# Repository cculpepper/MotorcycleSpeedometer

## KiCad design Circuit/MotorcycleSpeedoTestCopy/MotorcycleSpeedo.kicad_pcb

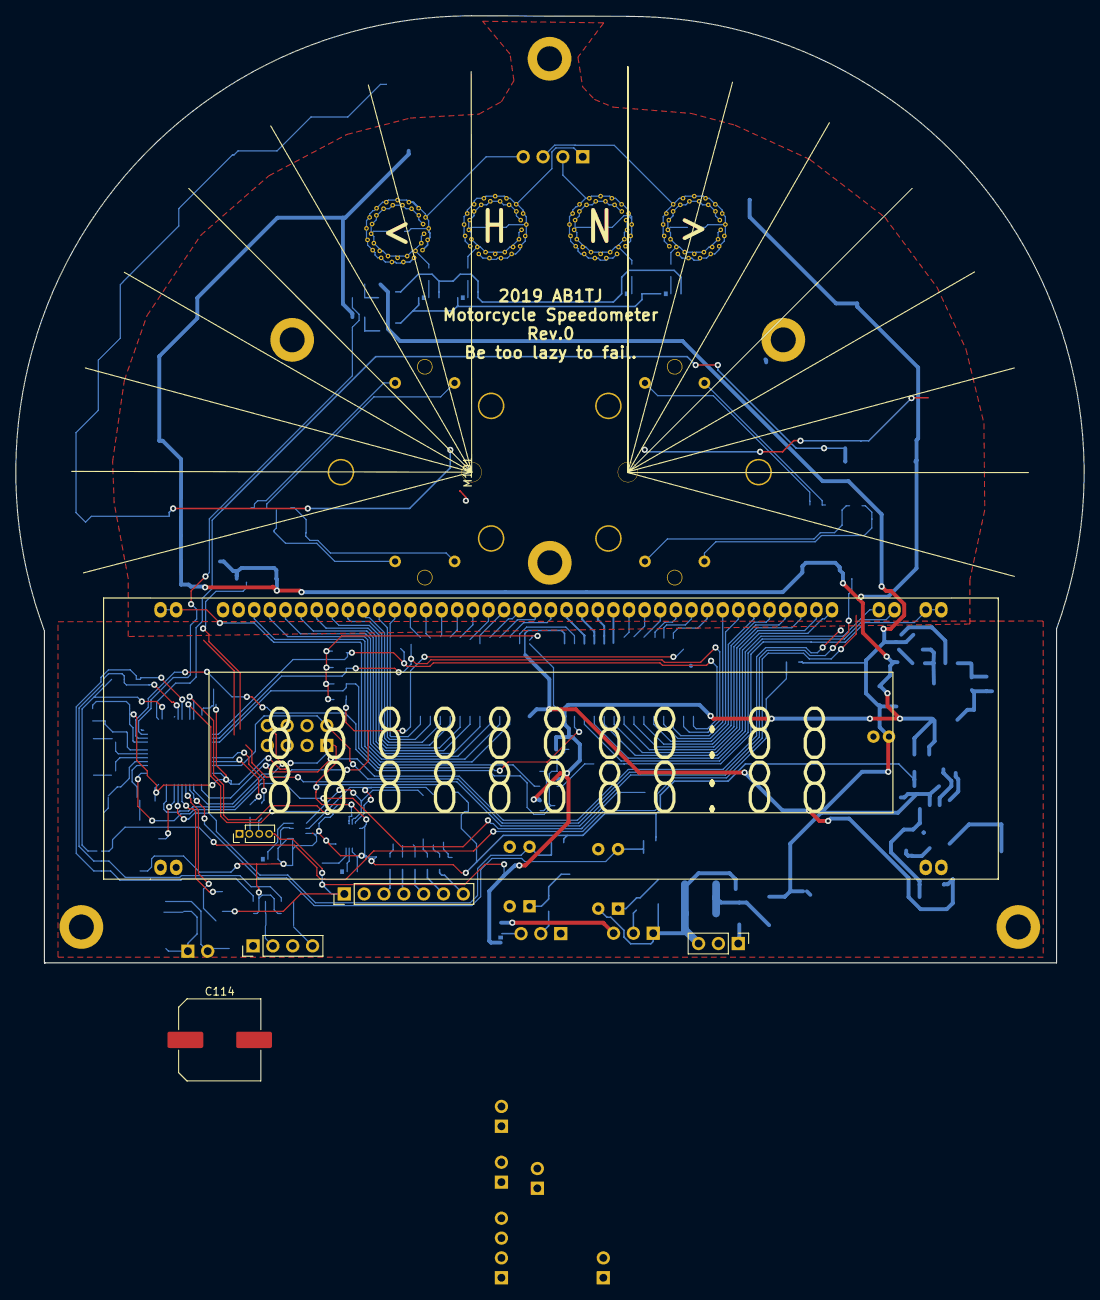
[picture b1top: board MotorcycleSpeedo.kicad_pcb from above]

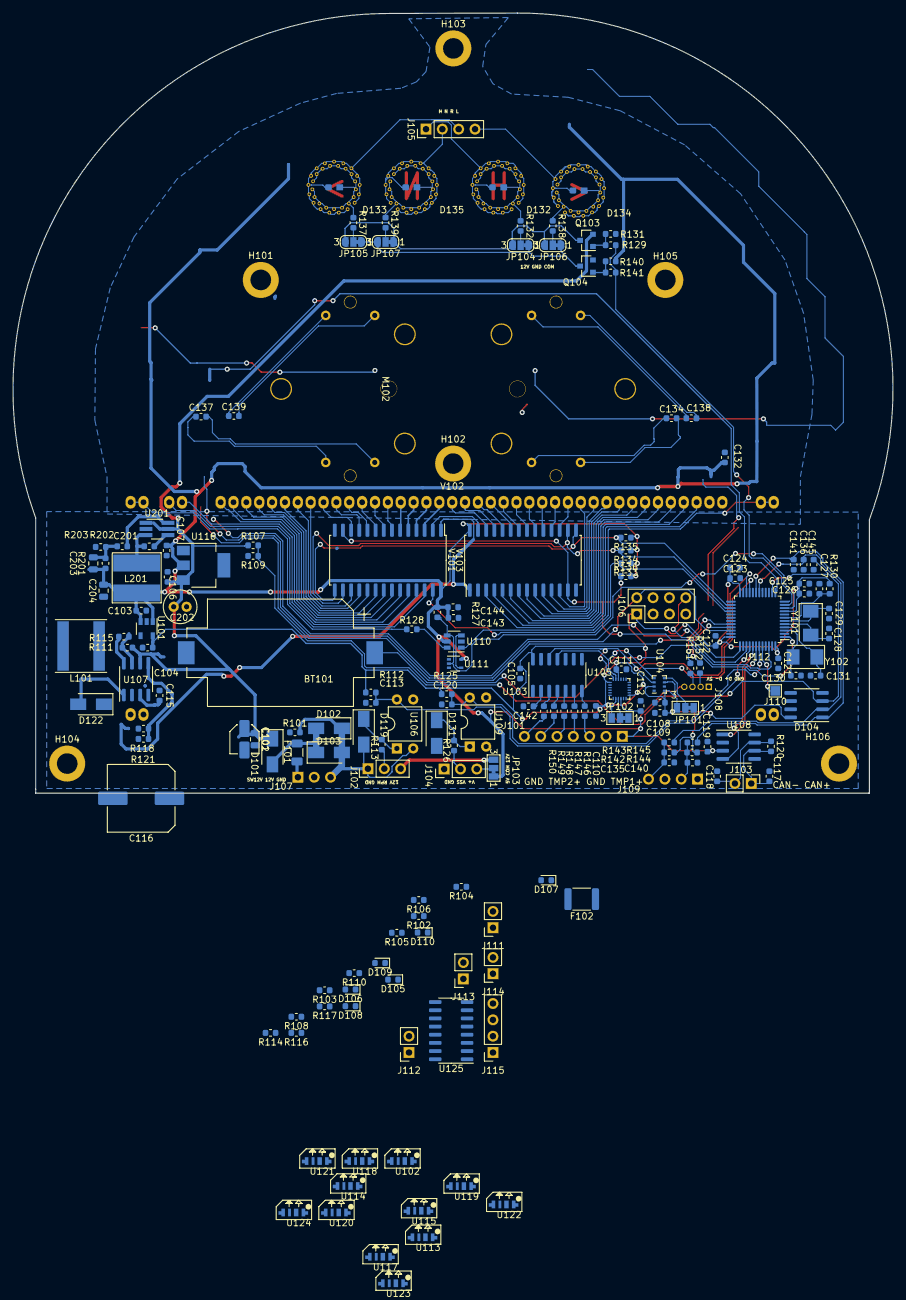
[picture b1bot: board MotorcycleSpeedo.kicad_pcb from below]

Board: 2 copper layers, 136.8 x 121.3 mm, 184 parts (167 on the bottom side), 159 nets.

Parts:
BT101: Battery_Cell; BatteryHolder_Keystone_1060_1x2032
C101: C; C_0805_2012Metric
C102: 33uH; C_Elec_4x5.4
C103, C104, C106, C107, C108, C110, C113, C117, C118, C119, C120, C121, C122, C132, C145: C; C_0603_1608Metric
C105, C134, C137, C138, C139, C143, C144: .1uF; C_0603_1608Metric
C109, C111, C112: .1uf; C_0603_1608Metric
C114: CP1; C_Elec_10x10.2
C115: 680pf; C_0603_1608Metric
C116: 330uF; C_Elec_10x10.2
C123, C126, C127, C135, C140: 0.1uF; C_0603_1608Metric
C124, C125, C201: 1uF; C_0603_1608Metric
C128, C129: 20pF; C_0603_1608Metric
C130, C131: 9pF; C_0603_1608Metric
C136, C141: 0.22uF; C_0603_1608Metric
C142: .01uF; C_0603_1608Metric
C202: 22uF; C_Radial_D5.0mm_H11.0mm_P2.00mm
C203: DNP; C_0805_2012Metric
C204: 22uF; C_0805_2012Metric
D101, D102: D_Schottky; D_SMA
D103: D_TVS; D_SMA
D104: SP721; SOIC-8_3.9x4.9mm_P1.27mm
D105, D106, D107, D108, D109, D110: LED; LED_0603_1608Metric
D119, D122, D131: D; D_SMA
D132: HIGH; HF.SilkSF.Cu
D133: RIGHT; RightPointingF.SilkSF.Cu
D134: LEFT; LeftPointingF.SilkSF.Cu
D135: NEUTRAL; NF.SilkSF.Cu
F101: Polyfuse; Fuse_1206_3216Metric
F102: Polyfuse; Fuse_1812_4532Metric
H101, H102, H103, H104, H105, H106: MountingHole_Pad; MountingHole_3.2mm_M3_DIN965_Pad
J101: Conn_01x07_Female; PinHeader_1x07_P2.54mm_Vertical
J102, J104, J107: Conn_01x03_Female; PinHeader_1x03_P2.54mm_Vertical
J103: Conn_01x02_Female; PinHeader_1x02_P2.54mm_Vertical
J105, J109: Conn_01x04_Female; PinHeader_1x04_P2.54mm_Vertical
J106: Conn_02x04_Counter_Clockwise; PinHeader_2x04_P2.54mm_Vertical
J108: Conn_01x04_Male; PinHeader_1x04_P1.27mm_Vertical
J110: Conn_01x01_Female; TestPoint_Pad_1.5x1.5mm
J111, J112, J113, J114: Conn_01x02_Male; PinSocket_1x02_P2.54mm_Vertical
J115: Conn_01x04_Female; PinSocket_1x04_P2.54mm_Vertical
JP101, JP102, JP103: SolderJumper_3_Bridged12; SolderJumper-3_P1.3mm_Bridged12_Pad1.0x1.5mm_NumberLabels
JP104, JP105, JP106, JP107: SolderJumper_3_Bridged12; SolderJumper-3_P1.3mm_Bridged12_RoundedPad1.0x1.5mm_NumberL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
L101: 330uh; L_Taiyo-Yuden_NR-80xx
L201: 10uH; CDRH6D28
M101, M102: Stepper_Motor_bipolar; x25FrontStepper
Q103: Q_PMOS_GSD; SOT-23
Q104: Q_NMOS_GSD; SOT-23
R101, R110, R113, R117, R126, R127, R128, R130, R132, R137, R138, R139: R; R_0603_1608Metric
R102, R103, R104, R105, R106, R108: 1K; R_0603_1608Metric
R107, R112, R114, R116, R125, R131, R133, R134, R135, R136, R140: 10K; R_0603_1608Metric
R109, R143, R145: 470; R_0603_1608Metric
R111: .22; R_0603_1608Metric
R115: 180; R_0603_1608Metric
R118, R202: 59K; R_0603_1608Metric
R120: 120; R_0603_1608Metric
R121, R142, R144: 2.49K; R_0603_1608Metric
R129, R141: 1k; R_0603_1608Metric
R146, R147, R148, R149, R150: 560; R_0603_1608Metric
R151, R152: 22; R_0603_1608Metric
R201: 40.2K; R_0603_1608Metric
R203: 13K; R_0603_1608Metric
U101: AP131-33; SOT-23-5
U102, U113, U114, U115, U117, U118, U119, U120, U121, U122, U123, U124: SK6812-A; SK6812-SideA
U103: APT8L08; SOIC-14_3.9x8.7mm_P1.27mm
U104: BMP280; Bosch_LGA-8_2x2.5mm_P0.65mm_ClockwisePinNumbering
U105: MPU-9250; InvenSense_QFN-24_3x3mm_P0.4mm
U106, U109: LTV-817; DIP-4_W7.62mm
U107: MC34063AD; SOIC-8_3.9x4.9mm_P1.27mm
U108: TJA1051T-E; SOIC-8_3.9x4.9mm_P1.27mm
U110: FM116B; SOT-23-6
U111: 74AHCT1G14; SOT-353_SC-70-5
U112: STM32F103C8Tx; LQFP-48_7x7mm_P0.5mm
U116: AMS1117-5.0; SOT-223
U125: VID6608; SOIC-16_3.9x9.9mm_P1.27mm
U201: AP65111AWU; TSOT-23-6_HandSoldering
V101, V103: HV5812; SOIC-28W_7.5x17.9mm_P1.27mm
V102: HNA-12MM54T
Y101: 8M; Crystal_SMD_5032-2Pin_5.0x3.2mm
Y102: 32K; Crystal_SMD_5032-2Pin_5.0x3.2mm

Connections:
+3V3: C104.2, C105.1, C108.1, C109.1, C110.1, C111.1, C121.1, C122.1, C123.1, C124.1, C125.1, C126.1, D104.8 (V+), J106.1, J111.1, JP101.3 (B), JP102.3 (B), R105.1, R112.1, R125.1, R130.2, R142.1, R144.1, U101.5 (OUT), U103.14 (VDD), U104.2 (CSB), U104.6 (VDDIO), U104.8 (VDD), U105.1 (RESV_VDDIO), U105.8 (VDDIO), U105.13 (VDD), U105.22 (~CS), U112.9 (VDDA), U112.24 (VDD), U112.36 (VDD), U112.48 (VDD)
+5V: BT101.2 (-), C101.2, C102.2, C103.1, C103.2, C104.1, C105.2, C106.2, C107.1, C107.2, C108.2, C109.2, C110.2, C111.2, C112.2, C113.2, C114.2, C115.2, C116.2, C117.2, C118.2, C119.1, C119.2, C120.2, C121.2, C122.2, C123.2, C124.2, C125.2, C126.2, C127.2, C128.2, C129.2, C130.2, C131.2, C132.1, C132.2, C135.2, C136.2, C140.2, C141.2, C142.1, C143.1, C143.2, C144.1, C144.2, C145.2, C202.2, C203.2, C204.1, C204.2, D104.4 (V-), D106.1 (K), D107.1 (K), D108.1 (K), D109.1 (K), D110.1 (K), D131.2 (A), H101.1, H102.1, H103.1, H104.1, H105.1, H106.1, J101.1, J101.2, J104.1, J106.7, J108.1, J108.4, J109.1, J109.3, J111.2, J112.2, J113.1, J113.2, J114.2, J115.4, JP101.1 (A), JP102.1 (A), JP103.1 (A), L201.2, Q104.2 (S), R101.1, R104.1, R109.2, R110.1, R114.2, R116.2, R117.2, R121.2, R127.1, R131.1, R133.1, R134.1, R135.1, R136.1, R136.2, R140.2, R201.1, R203.2, U101.1 (IN), U101.2 (GND), U101.3 (EN), U102.2 (VDD), U102.4 (GND), U103.1 (VSS), U104.1 (GND), U104.7 (GND), U105.11 (FSYNC), U105.18 (GND), U105.20 (RESV_GND), U106.3, U107.2 (SwE), U107.4 (GND), U108.2 (GND), U108.3 (VCC), U108.5 (EN), U109.2, U109.3, U110.2 (GND), U110.5 (V+), U111.3 (GND), U111.5 (VCC), U112.8 (VSSA), U112.17 (PA7), U112.23 (VSS), U112.35 (VSS), U112.46 (PB9), U112.47 (VSS), U113.2 (VDD), U113.4 (GND), U114.2 (VDD), U114.4 (GND), U115.2 (VDD), U115.4 (GND), U116.1 (GND), U116.2 (VO), U117.2 (VDD), U117.4 (GND), U118.2 (VDD), U118.4 (GND), U119.2 (VDD), U119.4 (GND), U120.2 (VDD), U120.4 (GND), U121.2 (VDD), U121.4 (GND), U122.2 (VDD), U122.4 (GND), U123.2 (VDD), U123.4 (GND), U124.2 (VDD), U124.4 (GND), U125.7 (VSS), U125.8 (VDD), U125.16 (VDD), U201.2 (GND), V101.13 (BLANK), V101.14 (GND), V101.26 (HV1), V101.28 (VDD/LV), V102.4 (1G), V103.13 (BLANK), V103.14 (GND), V103.28 (VDD/LV)
+12V: C101.1, C102.1, C106.1, C114.1, C202.1, D101.1 (K), J102.3, J112.1, JP103.3 (B), Q103.2 (S), R103.1, R107.1, R111.2, U107.6 (Vin), U116.3 (VI), U201.1 (VIN), U201.5 (EN)
/12V_Sense: C145.1, D104.3 (IN3), R107.2, R109.1, U112.14 (PA4)
/BOOT0: J110.1, R114.1, U112.44 (BOOT0)
/BOOT1: R116.1, U112.20 (PB2)
/CAN_RX: U108.4 (RXD), U112.41 (PB5)
/CAN_TX: U108.1 (TXD), U112.42 (PB6)
/HEARTBEAT: J106.6, R108.1, U112.38 (PA15)
/HIGH: D132.2 (A), J105.1
/HV_GRID: F102.2, J114.1, R106.1, V101.1 (VPP/HV), V103.1 (VPP/HV)
/IND_DIM: R129.1, R141.1, U112.11 (PA1)
/JTCK: J106.4, U112.37 (PA14), U125.2 (FSCXB)
/JTDO: J106.8, U112.39 (PB3)
/JTMS: J106.2, U112.34 (PA13), U125.1 (CWB)
/L_DIR: U112.30 (PA9), U125.9 (CWA)
/L_STP: U112.31 (PA10), U125.10 (FSCXA)
/L_TURN: D134.2 (A), J105.4
/NEUTRAL: D135.2 (A), J105.2
/RPM_OUT: C113.1, R112.2, U106.4, U112.40 (PB4)
/R_TURN: D133.2 (A), J105.3
/SCL: U103.11 (SCL), U104.4 (SCK), U105.23 (SCL/SCLK), U112.21 (PB10)
/SDA: U103.12 (SDA), U104.3 (SDI), U105.24 (SDA/MOSI), U112.22 (PB11)
/STP1: C134.1, M101.1, U125.3 (OUT1A)
/STP2: C134.2, M101.2 (-), U125.4 (OUT2A)
/STP3: C138.2, M101.3, U125.6 (OUT3A)
/STP4: C138.1, M101.4, U125.5 (OUT4A)
/STP5: C137.1, M102.2 (-), U125.11 (OUT1B)
/STP6: C137.2, M102.1, U125.12 (OUT2B)
/STP7: C139.1, M102.4, U125.14 (OUT3B)
/STP8: C139.2, M102.3, U125.13 (OUT4B)
/STP_RST: R117.1, U125.15 (~RST)
/SWITCHED_12V: F101.1, J107.1, R102.1
/TEMP1+: C135.1, J109.4, R142.2, R143.1
/TEMP1_OUT: C136.1, D104.2 (IN2), R143.2, U112.18 (PB0)
/TEMP2+: C140.1, J109.2, R144.2, R145.1
/TEMP2_OUT: C141.1, D104.1 (IN1), R145.2, U112.19 (PB1)
/USB-D+: R152.1, U112.33 (PA12)
/USB-D-: R151.1, U112.32 (PA11)
/VFD_FILAMENT_A: R127.2, U110.4 (IN_A), U111.2, U112.10 (PA0)
/VFD_LV_CLK: J115.3, R135.2, U112.26 (PB13), V101.15 (CLK), V103.15 (CLK)
/VFD_LV_MOSI: J115.1, R133.2, U112.28 (PB15), V101.27 (SDI)
/VFD_LV_STROBE: J115.2, R134.2, U112.27 (PB14), V101.16 (STROBe), V103.16 (STROBe)
/VSS_OUT: C120.1, R125.2, U109.4, U112.43 (PB7)
GNDPWR: D102.2 (A), D103.1 (A1), D105.1 (K), D119.2 (A), J102.1, J107.3, R101.2, U106.2
unnamed: BT101.1 (+), U112.1 (VBAT)
unnamed: C112.1, U105.10 (REGOUT)
unnamed: C115.1, U107.3 (TC)
unnamed: C116.1, D122.1 (K), F102.1, R118.1
unnamed: C117.1, J103.1, R120.2, U108.6 (CANL)
unnamed: C118.1, J103.2, R120.1, U108.7 (CANH)
unnamed: C127.1, R130.1, U112.7 (NRST)
unnamed: C128.1, U112.5 (PD0), Y101.2
unnamed: C129.1, U112.6 (PD1), Y101.1
unnamed: C130.1, U112.3 (PC14), Y102.2
unnamed: C131.1, U112.4 (PC15), Y102.1
unnamed: C142.2, U103.2 (CO)
unnamed: C201.1, U201.4 (BST)
unnamed: C201.2, L201.1, U201.3 (SW)
unnamed: C203.1, R201.2, R202.2, R203.1
unnamed: D101.2 (A), D102.1 (K), D103.2 (A2), F101.2
unnamed: D105.2 (A), R102.2
unnamed: D106.2 (A), R103.2
unnamed: D107.2 (A), R104.2
unnamed: D108.2 (A), R105.2
unnamed: D109.2 (A), R106.2
unnamed: D110.2 (A), R108.2
unnamed: D119.1 (K), R113.2, U106.1
unnamed: D122.2 (A), L101.2, U107.1 (SwC)
unnamed: D131.1 (K), R126.2, U109.1
unnamed: D132.1 (K), R132.1
unnamed: D133.1 (K), R137.1
unnamed: D134.1 (K), R138.1
unnamed: D135.1 (K), R139.1
unnamed: J101.3, R146.1
unnamed: J101.4, R147.1
unnamed: J101.5, R148.1
unnamed: J101.6, R149.1
unnamed: J101.7, R150.1
unnamed: J102.2, R113.1
unnamed: J104.2, R126.1
unnamed: J104.3, JP103.2 (C)
unnamed: J108.2, R152.2
unnamed: J108.3, R151.2
unnamed: JP101.2 (C), U104.5 (SDO)
unnamed: JP102.2 (C), U105.9 (AD0/MISO)
unnamed: JP104.1 (A), JP105.1 (A), JP106.1 (A), JP107.3 (B), Q104.3 (D)
unnamed: JP104.2 (C), R132.2
unnamed: JP104.3 (B), JP105.3 (B), JP106.3 (B), JP107.1 (A), Q103.3 (D)
unnamed: JP105.2 (C), R137.2
unnamed: JP106.2 (C), R138.2
unnamed: JP107.2 (C), R139.2
unnamed: L101.1, R111.1, R115.1, U107.7 (Ipk)
unnamed: Q103.1 (G), R129.2, R131.2
unnamed: Q104.1 (G), R140.1, R141.2
unnamed: R110.2, U102.1 (DIN)
unnamed: R115.2, U107.8 (DC)
unnamed: R118.2, R121.1, U107.5 (Vfb)
unnamed: R128.1, V102.1 (F1), V102.2 (F1)
unnamed: R128.2, U110.6 (OUT_A)
unnamed: R146.2, U103.7 (K04)
unnamed: R147.2, U103.6 (K03)
unnamed: R148.2, U103.5 (K02)
unnamed: R149.2, U103.4 (K01)
unnamed: R150.2, U103.3 (K00)
unnamed: R202.1, U201.6 (FB)
unnamed: U102.3 (DOUT), U113.1 (DIN)
unnamed: U110.1 (OUT_B), V102.50 (F2), V102.51 (F2)
unnamed: U110.3 (IN_B), U111.4
unnamed: U113.3 (DOUT), U114.1 (DIN)
unnamed: U114.3 (DOUT), U115.1 (DIN)
unnamed: U115.3 (DOUT), U117.1 (DIN)
unnamed: U117.3 (DOUT), U118.1 (DIN)
unnamed: U118.3 (DOUT), U119.1 (DIN)
unnamed: U119.3 (DOUT), U120.1 (DIN)
unnamed: U120.3 (DOUT), U121.1 (DIN)
unnamed: U121.3 (DOUT), U122.1 (DIN)
unnamed: U122.3 (DOUT), U123.1 (DIN)
unnamed: U123.3 (DOUT), U124.1 (DIN)
unnamed: V101.2 (SDO), V103.27 (SDI)
unnamed: V101.3 (HV20), V102.25 (P8)
unnamed: V101.4 (HV19), V102.24 (P7)
unnamed: V101.5 (HV18), V102.23 (P6)
unnamed: V101.6 (HV17), V102.22 (P5)
unnamed: V101.7 (HV16), V102.21 (P4)
unnamed: V101.8 (HV15), V102.20 (P3)
unnamed: V101.9 (HV14), V102.19 (P2)
unnamed: V101.10 (HV13), V102.18 (P1)
unnamed: V101.11 (HV12), V102.17 (12G)
unnamed: V101.12 (HV11), V102.16 (11G)
unnamed: V101.17 (HV10), V102.15 (10G)
unnamed: V101.18 (HV9), V102.14 (9G)
unnamed: V101.19 (HV8), V102.13 (8G)
unnamed: V101.20 (HV7), V102.12 (7G)
unnamed: V101.21 (HV6), V102.11 (6G)
unnamed: V101.22 (HV5), V102.10 (5G)
unnamed: V101.23 (HV4), V102.9 (4G)
unnamed: V101.24 (HV3), V102.8 (3G)
unnamed: V101.25 (HV2), V102.5 (2G)
unnamed: V102.26 (P9), V103.26 (HV1)
unnamed: V102.27 (P10), V103.25 (HV2)
unnamed: V102.28 (P11), V103.24 (HV3)
unnamed: V102.29 (P12), V103.23 (HV4)
unnamed: V102.30 (P13), V103.22 (HV5)
unnamed: V102.31 (P14), V103.21 (HV6)
unnamed: V102.32 (P15), V103.20 (HV7)
unnamed: V102.33 (P16), V103.19 (HV8)
unnamed: V102.34 (P17), V103.18 (HV9)
unnamed: V102.35 (P18), V103.17 (HV10)
unnamed: V102.36 (P19), V103.12 (HV11)
unnamed: V102.37 (P20), V103.11 (HV12)
unnamed: V102.38 (P21), V103.10 (HV13)
unnamed: V102.39 (P22), V103.9 (HV14)
unnamed: V102.40 (P23), V103.8 (HV15)
unnamed: V102.41 (P24), V103.7 (HV16)
unnamed: V102.42 (P25), V103.6 (HV17)
unnamed: V102.43 (P26), V103.5 (HV18)
unnamed: V102.44 (P27), V103.4 (HV19)
unnamed: V102.45 (P28), V103.3 (HV20)

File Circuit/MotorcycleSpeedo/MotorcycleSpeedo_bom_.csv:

Component,Description,Part,References,Value,Footprint,Quantity Per PCB,Datasheet,Manufacturer PN
1,Single-cell battery,Battery_Cell,BT101,Battery_Cell,BatteryHolder_Keystone_1060_1x2032,1,~,CR2032-BS-6-1
2,Unpolarized capacitor,C,C130 C131,9pF,C_0603_1608Metric,2,~,
3,Unpolarized capacitor,C,C128 C129,20pF,C_0603_1608Metric,2,~,
4,Unpolarized capacitor,C,C115,680pf,C_0603_1608Metric,1,~,CC0603KRX7R0BB681
5,Unpolarized capacitor,C,C142,.01uF,C_0603_1608Metric,1,~,
6,Unpolarized capacitor,C,C105 C109 C111 C112 C123 C126 C127 C134 C135 C137 C138 C139 C140 C143 C144,.1uF,C_0603_1608Metric,15,~,
7,Unpolarized capacitor,C,C136 C141,0.22uF,C_0603_1608Metric,2,~,
8,Unpolarized capacitor,C,C124 C125 C201,1uF,C_0603_1608Metric,3,~,
9,Unpolarized capacitor,C,C202 C204,22uF,C_Elec_10x10.2,2,~,
10,Polarized capacitor,CP,C102,33uH,C_Elec_4x5.4,1,~,VE-330M1HTR-0806
11,Polarized capacitor,CP,C116,330uF,C_Elec_10x10.2,1,~,VZT331M1HTR-1010
12,Unpolarized capacitor,C,C101,C,C_0805_2012Metric,1,~,
13,Unpolarized capacitor,C,C103 C104 C106 C107 C108 C110 C113 C117 C118 C119 C120 C121 C122 C132 C145,C,C_0603_1608Metric,15,~,
14,"Polarized capacitor, US symbol",CP1,C114,CP1,C_Elec_10x10.2,1,~,
15,Diode,D,D119 D122 D131,D,D_SMA,3,~,C38653
16,Schottky diode,D_Schottky,D101 D102,D_Schottky,D_SMA,2,~,
17,Bidirectional transient-voltage-suppression diode,D_TVS,D103,D_TVS,D_SMA,1,~,
18,Light emitting diode,LED,D132,HIGH,HF.SilkSF.Cu,1,~,
19,Light emitting diode,LED,D105 D106 D107 D108 D109 D110,LED,LED_0603_1608Metric,6,~,
20,Light emitting diode,LED,D134,LEFT,LeftPointingF.SilkSF.Cu,1,~,
21,Light emitting diode,LED,D135,NEUTRAL,NF.SilkSF.Cu,1,~,
22,Light emitting diode,LED,D133,RIGHT,RightPointingF.SilkSF.Cu,1,~,
23,,SP721,D104,SP721,SOIC-8_3.9x4.9mm_P1.27mm,1,,
24,"Resettable fuse, polymeric positive temperature coefficient",Polyfuse,F101,Polyfuse,Fuse_1206_3216Metric,1,~,JK-NSMD100-16V
25,"Resettable fuse, polymeric positive temperature coefficient",Polyfuse,F102,Polyfuse,Fuse_1812_4532Metric,1,~,RF1334-000
26,"Generic connector, single row, 01x02, script generated (kicad-library-utils/schlib/autogen/connector/)",Conn_01x02_Female,J103,Conn_01x02_Female,PinHeader_1x02_P1.27mm_Vertical,1,~,
27,"Generic connector, single row, 01x02, script generated (kicad-library-utils/schlib/autogen/connector/)",Conn_01x02_Male,J111 J112 J113 J114,Conn_01x02_Male,PinSocket_1x02_P2.54mm_Vertical,4,~,
28,"Generic connector, single row, 01x03, script generated (kicad-library-utils/schlib/autogen/connector/)",Conn_01x03_Female,J102 J104 J107,Conn_01x03_Female,PinHeader_1x03_P2.54mm_Vertical,3,~,
29,"Generic connector, single row, 01x04, script generated (kicad-library-utils/schlib/autogen/connector/)",Conn_01x04_Female,J105,Conn_01x04_Female,PinHeader_1x04_P2.54mm_Vertical,1,~,
30,"Generic connector, single row, 01x04, script generated (kicad-library-utils/schlib/autogen/connector/)",Conn_01x04_Female,J109,Conn_01x04_Female,PinHeader_1x04_P1.27mm_Vertical,1,~,
31,"Generic connector, single row, 01x04, script generated (kicad-library-utils/schlib/autogen/connector/)",Conn_01x04_Female,J115,Conn_01x04_Female,PinSocket_1x04_P1.27mm_Vertical,1,~,
32,"Generic connector, single row, 01x04, script generated (kicad-library-utils/schlib/autogen/connector/)",Conn_01x04_Male,J108,Conn_01x04_Male,PinHeader_1x04_P1.27mm_Vertical,1,~,
33,"Generic connector, single row, 01x07, script generated (kicad-library-utils/schlib/autogen/connector/)",Conn_01x07_Female,J101,Conn_01x07_Female,PinSocket_1x07_P1.27mm_Vertical,1,~,
34,"Generic connector, double row, 02x04, odd/even pin numbering scheme (row 1 odd numbers, row 2 even numbers), script generated (kicad-library-utils/schlib/autogen/connector/)",Conn_02x04_Odd_Even,J106,Conn_02x04_Counter_Clockwise,PinHeader_2x04_P2.54mm_Vertical,1,~,
35,Inductor,L,L201,10uH,CDRH6D28,1,~,
36,Inductor,L,L101,330uh,L_Taiyo-Yuden_NR-80xx,1,~,SMNR8040-331MT
37,4-wire bipolar stepper motor,Stepper_Motor_bipolar,M101 M102,Stepper_Motor_bipolar,x25FrontStepper,2,http://www.infineon.com/dgdl/Application-Note-TLE8110EE_driv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,
38,"N-MOSFET transistor, gate/source/drain",Q_NMOS_GSD,Q104,Q_NMOS_GSD,SOT-23,1,~,NCE3400
39,"P-MOSFET transistor, gate/source/drain",Q_PMOS_GSD,Q103,Q_PMOS_GSD,SOT-23,1,~,
40,Resistor,R,R111,.22,R_0603_1608Metric,1,~,
41,Resistor,R,R151 R152,22,R_0603_1608Metric,2,~,
42,Resistor,R,R120,120,R_0603_1608Metric,1,~,
43,Resistor,R,R115,180,R_0603_1608Metric,1,~,
44,Resistor,R,R109 R143 R145,470,R_0603_1608Metric,3,~,
45,Resistor,R,R146 R147 R148 R149 R150,560,R_0603_1608Metric,5,~,
46,Resistor,R,R102 R103 R104 R105 R106 R108 R129 R141,1K,R_0603_1608Metric,8,~,
47,Resistor,R,R121 R142 R144,2.49K,R_0603_1608Metric,3,~,
48,Resistor,R,R107 R112 R114 R116 R125 R131 R133 R134 R135 R136 R140,10K,R_0603_1608Metric,11,~,
49,Resistor,R,R203,13K,R_0603_1608Metric,1,~,
50,Resistor,R,R201,40.2K,R_0603_1608Metric,1,~,
51,Resistor,R,R118 R202,59K,R_0603_1608Metric,2,~,
52,Resistor,R,R101 R110 R113 R117 R126 R127 R128 R130 R132 R137 R138 R139,R,R_0603_1608Metric,12,~,
53,"Single Schmitt NOT Gate, Low-Voltage CMOS",74AHCT1G14,U111,74AHCT1G14,SOT-353_SC-70-5,1,http://www.ti.com/lit/sg/scyt129e/scyt129e.pdf,
54,"1A Low Dropout regulator, positive, 5.0V fixed output, SOT-223",AMS1117-5.0,U116,AMS1117-5.0,SOT-223,1,http://www.advanced-monolithic.com/pdf/ds1117.pdf,SSP1117-5.0V
55,"300mA low dropout linear regulator, shutdown pin, 3.3V fixed positive output, SOT-23-5",AP131-33,U101,AP131-33,SOT-23-5,1,http://www.diodes.com/_files/datasheets/AP131.pdf,
56,,AP65111AWU,U201,AP65111AWU,TSOT-23-6_HandSoldering,1,,
57,,APT8L08,U103,APT8L08,SOIC-14_3.9x8.7mm_P1.27mm,1,DOCUMENTATION,
58,"Absolute Barometric Pressure Sensor, LGA-8",BMP280,U104,BMP280,Bosch_LGA-8_2x2.5mm_P0.65mm_ClockwisePinNumbering,1,https://ae-bst.resource.bosch.com/media/_tech/media/datashee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,
59,FM116B H Bridge,FM116B,U110,FM116B,SOT-23-6,1,https://datasheet.lcsc.com/szlcsc/Shenzhen-Fuman-Elec-FM116B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,
60,"DC Optocoupler, Vce 35V, CTR 50%, DIP-4",LTV-817,U106 U109,LTV-817,DIP-4_W7.62mm,2,http://www.us.liteon.com/downloads/LTV-817-827-847.PDF,
61,"1.5A, step-up/down/inverting switching regulator, 3-40V Vin, 100kHz, SO-8",MC34063AD,U107,MC34063AD,SOIC-8_3.9x4.9mm_P1.27mm,1,http://www.onsemi.com/pub_link/Collateral/MC34063A-D.PDF,
62,"InvenSense 9-Axis Motion Sensor, Accelerometer, Gyroscope, Compass, I2C/SPI",MPU-9250,U105,MPU-9250,InvenSense_QFN-24_3x3mm_P0.4mm,1,https://store.invensense.com/datasheets/invensense/MPU9250RE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,
63,,SK6812-A,U102 U113 U114 U115 U117 U118 U119 U120 U121 U122 U123 U124,SK6812-A,SK6812-SideA,12,,
64,"ARM Cortex-M3 MCU, 64KB flash, 20KB RAM, 72MHz, 2-3.6V, 37 GPIO, LQFP-48",STM32F103C8Tx,U112,STM32F103C8Tx,LQFP-48_7x7mm_P0.5mm,1,http://www.st.com/st-web-ui/static/active/en/resource/techni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,
65,"High-Speed CAN Transceiver, enable pin, silent mode, SOIC-8",TJA1051T-E,U108,TJA1051T-E,SOIC-8_3.9x4.9mm_P1.27mm,1,http://www.nxp.com/documents/data_sheet/TJA1051.pdf,"TJA1050T/CM,118"
66,,VID6608,U125,VID6608,SOIC-16_3.9x9.9mm_P1.27mm,1,http://47.110.239.244/UploadFile/down/2009111391710_VID6608%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,
67,,HNA-12MM54T,V102,HNA-12MM54T,HNA-12MM54T,1,DOCUMENTATION,HNA-12MM54T
68,,HV5812,V101 V103,HV5812,SOIC-28W_7.5x17.9mm_P1.27mm,2,DOCUMENTATION,
69,Two pin crystal,Crystal,Y102,32K,Crystal_SMD_5032-2Pin_5.0x3.2mm,1,~,Q13FC1350000300
70,Two pin crystal,Crystal,Y101,8M,Crystal_SMD_5032-2Pin_5.0x3.2mm,1,~,X50328MSB2GI





Component Groups:,71
Component Count:,170
Fitted Components:,169
Number of PCBs:,1
Total components:,169
Schematic Version:,
Schematic Date:,
PCB Variant:,['default']
BoM Date:,Sun 20 Sep 2020 01:09:59 PM EDT
Schematic Source:,MotorcycleSpeedo.kicad_sch
KiCad Version:,Eeschema (5.99.0-3329-ga80190e20)

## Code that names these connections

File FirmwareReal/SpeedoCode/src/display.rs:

#![no_std]
#![no_main]

extern crate panic_halt;


use embedded_graphics::image::Image16BPP;
use embedded_graphics::prelude::*;
use embedded_graphics::primitives::rectangle::Rectangle;

use embedded_graphics::fonts::Font6x8;
use embedded_graphics::text_6x8;

use riscv_rt::entry;
use gd32vf103_hal as hal;
use hal::prelude::*;
use hal::pac as pac;
use hal::spi::{Spi, Mode, Polarity, Phase};
use hal::delay;
use hal::ctimer;
use hal::rcu;
use embedded_hal::blocking::delay::DelayMs;
use st7735_lcd;
use st7735_lcd::Orientation;

#[entry]
fn main() -> ! {
    let dp = pac::Peripherals::take().unwrap();
    let mut rcu = dp.RCU.constrain();
    let mut gpioa = dp.GPIOA.split(&mut rcu.apb2);
    let mut gpiob = dp.GPIOB.split(&mut rcu.apb2);
    let clocks = rcu::Strict::new().freeze(&mut rcu.cfg);
    let ctimer = ctimer::CoreTimer::new(dp.CTIMER);;
    let mut delay = delay::Delay::new(clocks, ctimer);
    let sck = gpioa.pa5.into_alternate_push_pull(&mut gpioa.ctl0);
    let miso = gpioa.pa6.into_floating_input(&mut gpioa.ctl0);
    let mosi = gpioa.pa7.into_alternate_push_pull(&mut gpioa.ctl0);
    let nss = gpioa.pa4.into_alternate_push_pull(&mut gpioa.ctl0);
    let spi_mode = Mode {
        polarity: Polarity::IdleLow,
        phase: Phase::CaptureOnFirstTransition
    };
    let spi = Spi::spi0(
                        dp.SPI0,
                        (sck,miso,mosi,nss),
                        spi_mode,
                        1.mhz(),
                        clocks,
                        &mut rcu.apb2
                      );
    let tft_rst_pin = gpiob.pb1.into_push_pull_output(&mut gpiob.ctl0);
    let tft_rs_pin = gpiob.pb0.into_push_pull_output(&mut gpiob.ctl0); // Data or command select
    let tft_cs_pin = gpiob.pb2.into_push_pull_output(&mut gpiob.ctl0);
    // let mut spi = hal::spi()
    let mut disp = st7735_lcd::ST7735::new(spi, tft_rs_pin, tft_rst_pin,true, true);
    disp.init(&mut delay).unwrap();
    disp.set_orientation(&Orientation::Landscape).unwrap();
    let black_backdrop = Rectangle::new(Coord::new(0, 0), Coord::new(160, 120)).fill(Some(0xffffu16.into()));

    disp.draw(black_backdrop.into_iter());

    // let ferris = Image16BPP::new(include_bytes!("./ferris.raw"), 86, 64).translate(Coord::new(40, 33));

    // disp.draw(ferris.into_iter());

    disp.draw(text_6x8!("Hello Rust!").into_iter());

    disp.draw(Font6x8::render_str("Test!"));

    // disp.draw(
        // Font6x8::render_str("Test!")
        // .translate(Coord::new(30,30))
        // .fill(Some(1u8))
        // .stroke(Some(0u8)).into_iter());

    loop {}
}

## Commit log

2019-05-20 Initial commit. Board is schematically done, may have screwed up a submodule initialization.
2019-07-31 made some schematic changes, close to finishing and getting ready to send it to fab
2019-11-06 Board built enough to submit. I'm sure changes will be made.
2019-11-10 Modified the board.
    I noticed I had the TDI and TMS? lines PA14 and PA15 switched. I
    modified the schematic and board. They should both match what was
    actually created.
2020-09-21 Finished rev 1 of the board, changed motor drivers, moved power supply stouff, fixed programming header layout, added power indication LEDS
2022-02-16 Committing what was saved before. No idea what? It's been a while...
2022-02-16 Some general cleanup
2022-02-16 Adedd the real code, should be in firmwareReal
2022-02-16 More cleanup
2022-04-08 Moved reference to libroary
2022-04-08 Maybe fixed lib again
2022-04-08 Try 2
2022-04-08 continuing shit
2022-04-08 blah x3
2022-04-08 FINALLY ADDED THE SUBMODULE
